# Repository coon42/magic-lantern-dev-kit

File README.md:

# magic-lantern-dev-kit
A dev kit for connection and communication with the service port of Canon EOS cameras.

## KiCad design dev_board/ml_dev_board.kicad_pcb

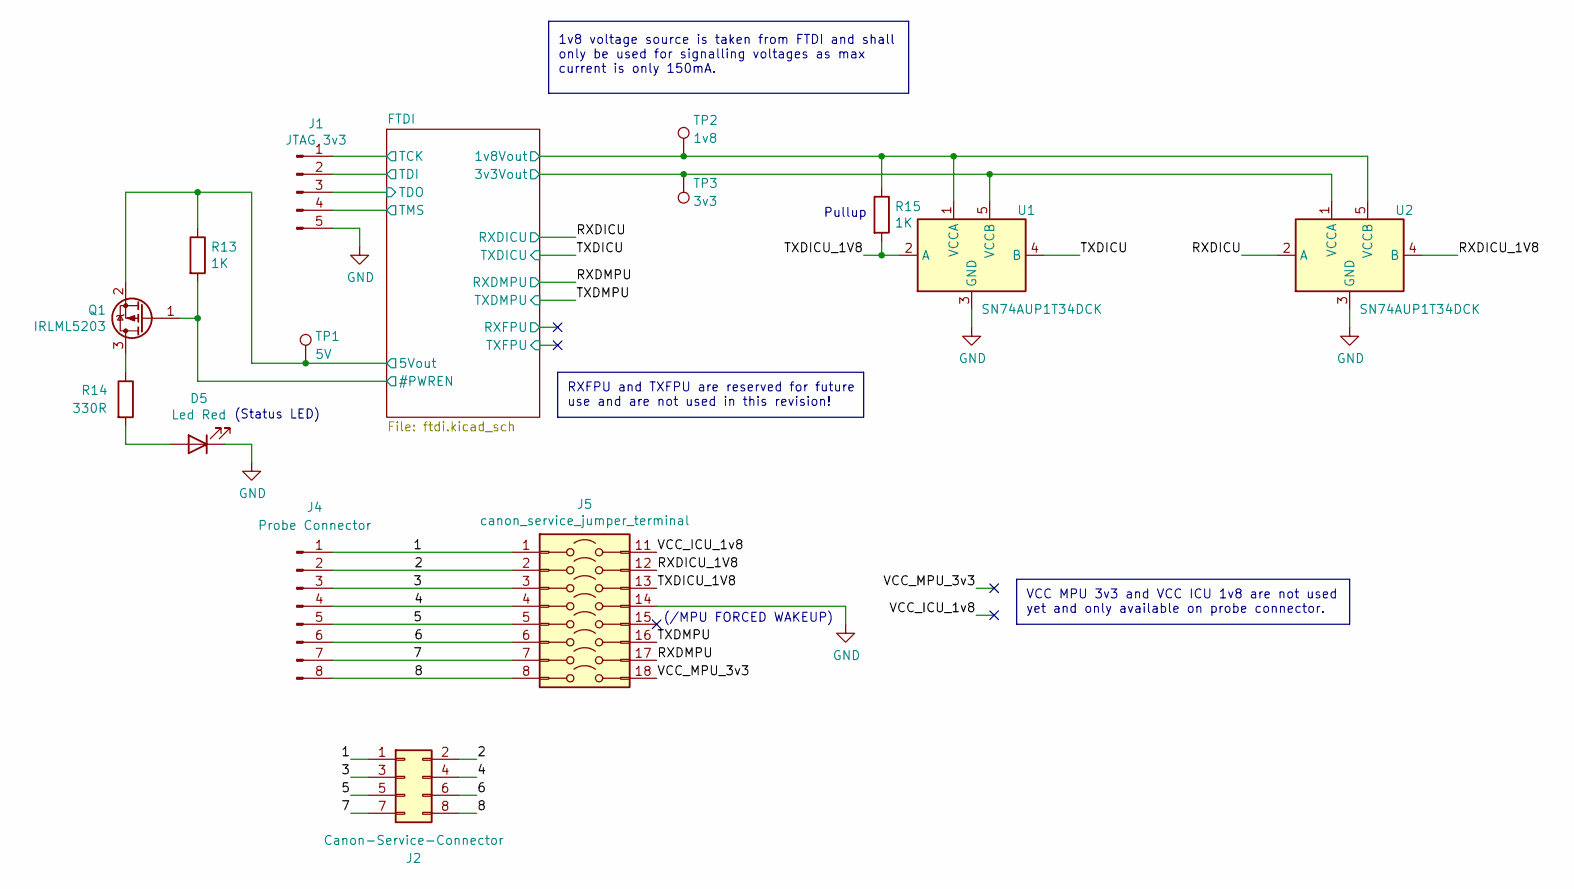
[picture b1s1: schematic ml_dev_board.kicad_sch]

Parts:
D5: Led Red; LED_0805_2012Metric
J1: JTAG 3v3; PinHeader_1x05_P2.54mm_Vertical_SMD_Pin1Left
J2: Canon-Service-Connector; IDC-Header_2x04_P2.54mm_Vertical
J4: Probe Connector; PinHeader_1x08_P2.54mm_Vertical_SMD_Pin1Left
J5: canon_service_jumper_terminal; PinHeader_2x08_P2.54mm_Vertical_Jumper_SMD
Q1: IRLML5203; SOT-23
R13, R15: 1K; R_0805_2012Metric
R14: 330R; R_0805_2012Metric
TP1: 5V; TestPoint_Pad_D1.5mm
TP2: 1v8; TestPoint_Pad_D1.5mm
TP3: 3v3; TestPoint_Pad_D1.5mm
U1, U2: SN74AUP1T34DCK; SOT-353_SC-70-5

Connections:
+1V8: R15.1, TP2.1, U1.1 (VCCA), U2.5 (VCCB); also elsewhere on the board
+3V3: TP3.1, U1.5 (VCCB), U2.1 (VCCA); also elsewhere on the board
+5V: Q1.2 (S), R13.1, TP1.1; also elsewhere on the board
/1: J2.1, J4.1, J5.1
/2: J2.2, J4.2, J5.2
/3: J2.3, J4.3, J5.3
/4: J2.4, J4.4, J5.4
/5: J2.5, J4.5, J5.5
/6: J2.6, J4.6, J5.6
/7: J2.7, J4.7, J5.7
/8: J2.8, J4.8, J5.8
/FTDI/#PWREN: Q1.1 (G), R13.2; also elsewhere on the board
/FTDI/TCK: J1.1; also elsewhere on the board
/FTDI/TDI: J1.2; also elsewhere on the board
/FTDI/TDO: J1.3; also elsewhere on the board
/FTDI/TMS: J1.4; also elsewhere on the board
/RXDICU: U2.2 (A); also elsewhere on the board
/RXDICU_1V8: J5.12, U2.4 (B)
/RXDMPU: J5.17; also elsewhere on the board
/TXDICU: U1.4 (B); also elsewhere on the board
/TXDICU_1V8: J5.13, R15.2, U1.2 (A)
/TXDMPU: J5.16; also elsewhere on the board
/VCC_ICU_1v8: J5.11
/VCC_MPU_3v3: J5.18
GND: D5.1 (K), J1.5, J5.14, U1.3 (GND), U2.3 (GND); also elsewhere on the board
unnamed: D5.2 (A), R14.2
unnamed: Q1.3 (D), R14.1

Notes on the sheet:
Pullup
RXFPU and TXFPU are reserved for future use and are not used in this revision!
(/MPU FORCED WAKEUP)
(Status LED)
1v8 voltage source is taken from FTDI and shall only be used for signalling voltages as max current is only 150mA.
VCC MPU 3v3 and VCC ICU 1v8 are not used yet and only available on probe connector.

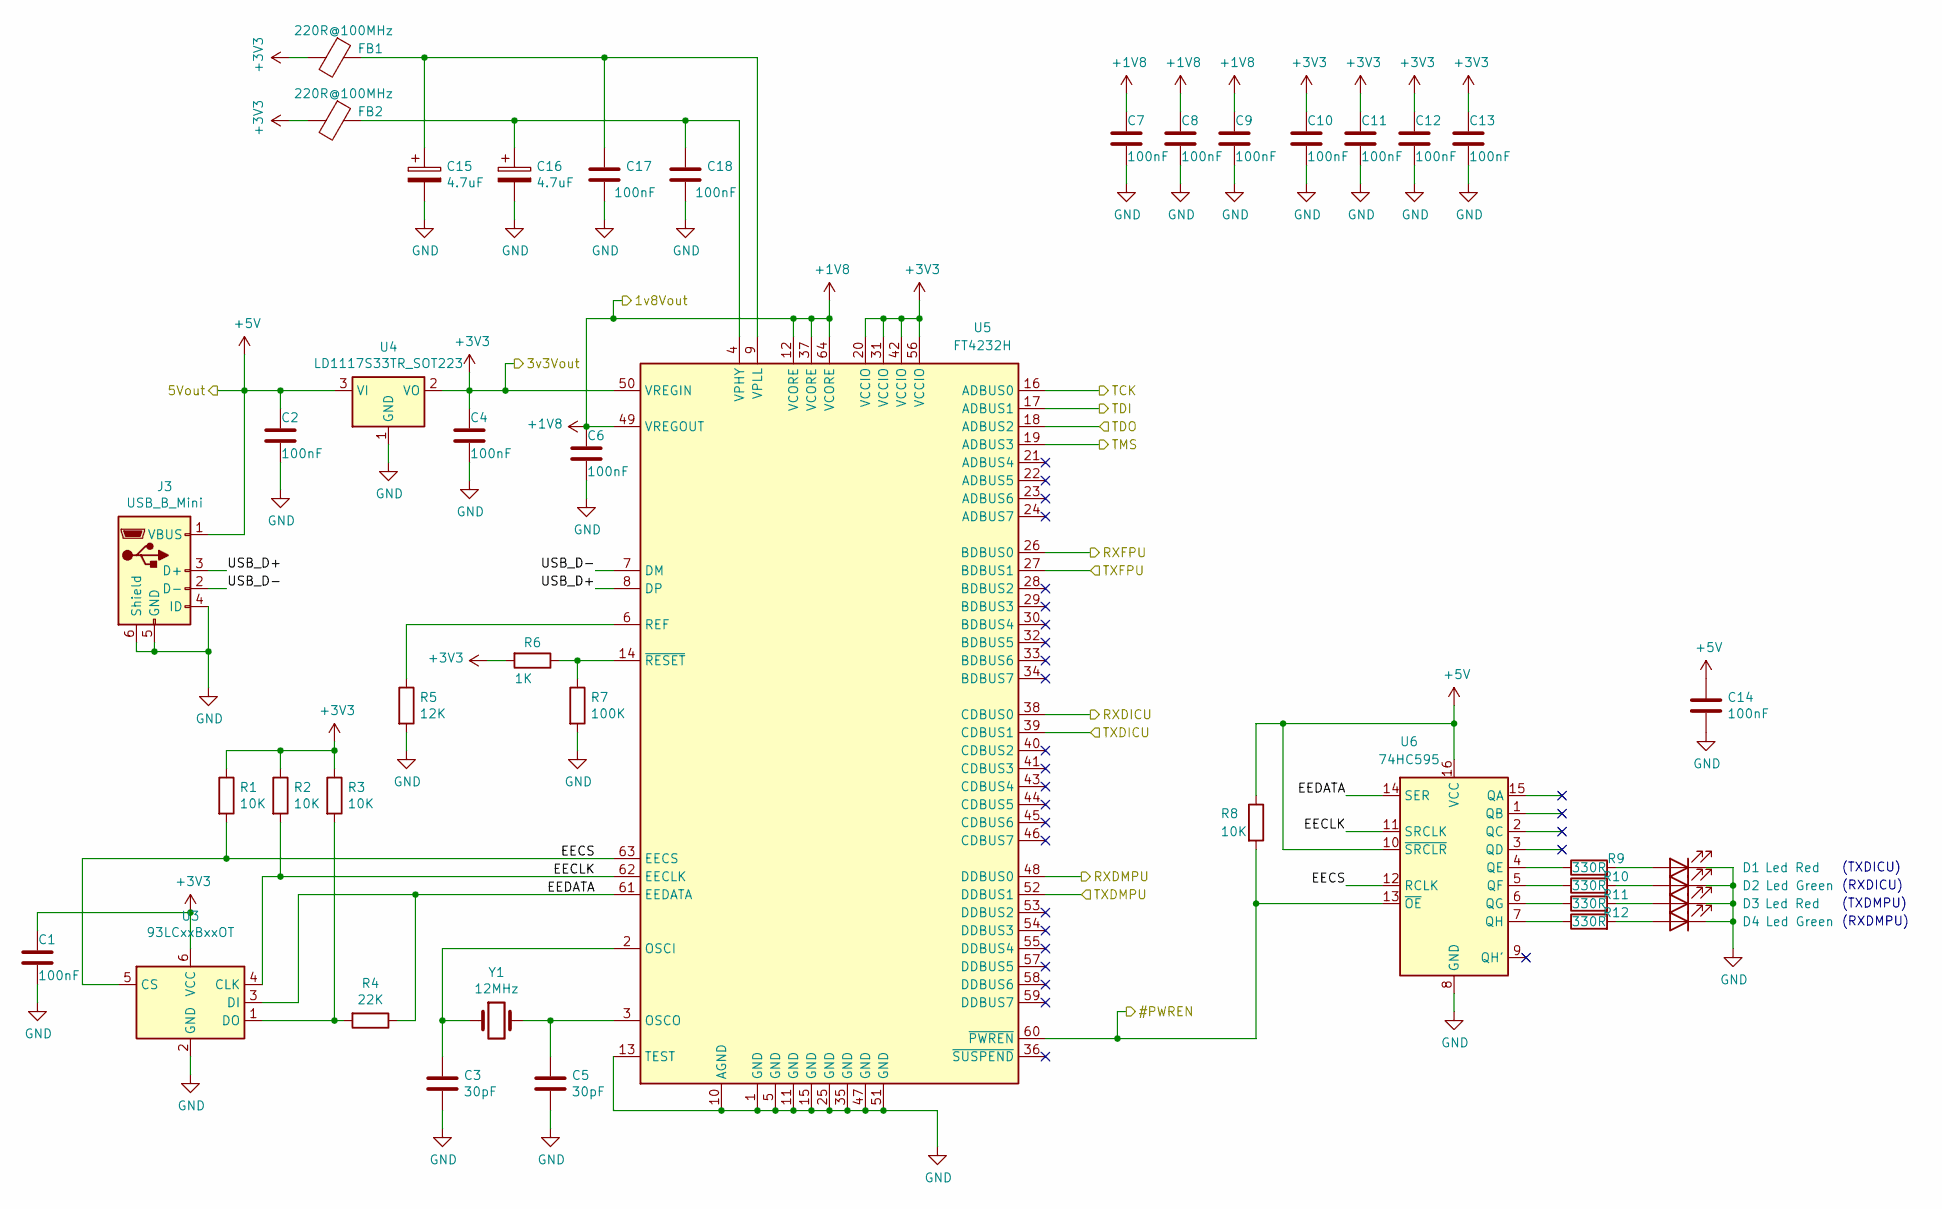
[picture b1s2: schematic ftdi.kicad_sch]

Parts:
C1, C2, C4, C6, C7, C8, C9, C10, C11, C12, C13, C14, C17, C18: 100nF; C_0805_2012Metric
C3, C5: 30pF; C_0805_2012Metric
C15, C16: 4.7uF; CP_EIA-3216-18_Kemet-A
D1, D3: Led Red; LED_0805_2012Metric
D2, D4: Led Green; LED_0805_2012Metric
FB1, FB2: 220R@100MHz; L_0805_2012Metric
J3: USB_B_Mini; USB_Mini-B_Lumberg_2486_01_Horizontal
R1, R2, R3, R8: 10K; R_0805_2012Metric
R4: 22K; R_0805_2012Metric
R5: 12K; R_0805_2012Metric
R6: 1K; R_0805_2012Metric
R7: 100K; R_0805_2012Metric
R9, R10, R11, R12: 330R; R_0805_2012Metric
U3: 93LCxxBxxOT; SOT-23-6
U4: LD1117S33TR_SOT223; SOT-223-3_TabPin2
U5: FT4232H; LQFP-64-1EP_10x10mm_P0.5mm_EP6.5x6.5mm_no_central_solder_pad
U6: 74HC595; TSSOP-16_4.4x5mm_P0.65mm
Y1: 12MHz; Crystal_SMD_TXC_7M-4Pin_3.2x2.5mm

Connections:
+1V8: C6.1, C7.1, C8.1, C9.1, U5.12 (VCORE), U5.37 (VCORE), U5.49 (VREGOUT), U5.64 (VCORE); also elsewhere on the board
+3V3: C1.1, C4.1, C10.1, C11.1, C12.1, C13.1, FB1.2, FB2.2, R1.1, R2.1, R3.1, R6.2, U3.6 (VCC), U4.2 (VO), U5.20 (VCCIO), U5.31 (VCCIO), U5.42 (VCCIO), U5.50 (VREGIN), U5.56 (VCCIO); also elsewhere on the board
+5V: C2.1, C14.1, J3.1 (VBUS), R8.1, U4.3 (VI), U6.10 (~SRCLR), U6.16 (VCC); also elsewhere on the board
/FTDI/#PWREN: R8.2, U5.60 (~PWREN), U6.13 (~OE); also elsewhere on the board
/FTDI/EECLK: R2.2, U3.4 (CLK), U5.62 (EECLK), U6.11 (SRCLK)
/FTDI/EECS: R1.2, U3.5 (CS), U5.63 (EECS), U6.12 (RCLK)
/FTDI/EEDATA: R4.1, U3.3 (DI), U5.61 (EEDATA), U6.14 (SER)
/FTDI/RXFPU: U5.26 (BDBUS0)
/FTDI/TCK: U5.16 (ADBUS0); also elsewhere on the board
/FTDI/TDI: U5.17 (ADBUS1); also elsewhere on the board
/FTDI/TDO: U5.18 (ADBUS2); also elsewhere on the board
/FTDI/TMS: U5.19 (ADBUS3); also elsewhere on the board
/FTDI/TXFPU: U5.27 (BDBUS1)
/FTDI/USB_D+: J3.3 (D+), U5.8 (DP)
/FTDI/USB_D-: J3.2 (D-), U5.7 (DM)
/RXDICU: U5.38 (CDBUS0); also elsewhere on the board
/RXDMPU: U5.48 (DDBUS0); also elsewhere on the board
/TXDICU: U5.39 (CDBUS1); also elsewhere on the board
/TXDMPU: U5.52 (DDBUS1); also elsewhere on the board
GND: C1.2, C2.2, C3.2, C4.2, C5.2, C6.2, C7.2, C8.2, C9.2, C10.2, C11.2, C12.2, C13.2, C14.2, C15.2, C16.2, C17.2, C18.2, D1.1 (K), D2.1 (K), D3.1 (K), D4.1 (K), J3.4 (ID), J3.5 (GND), J3.6 (Shield), R5.2, R7.2, U3.2 (GND), U4.1 (GND), U5.1 (GND), U5.5 (GND), U5.10 (AGND), U5.11 (GND), U5.13 (TEST), U5.15 (GND), U5.25 (GND), U5.35 (GND), U5.47 (GND), U5.51 (GND), U6.8 (GND); also elsewhere on the board
unnamed: D1.2 (A), R9.2
unnamed: D2.2 (A), R10.2
unnamed: D3.2 (A), R11.2
unnamed: D4.2 (A), R12.2
unnamed: R3.2, R4.2, U3.1 (DO)
unnamed: C3.1, U5.2 (OSCI), Y1.1
unnamed: C5.1, U5.3 (OSCO), Y1.2
unnamed: R5.1, U5.6 (REF)
unnamed: C16.1, C18.1, FB2.1, U5.4 (VPHY)
unnamed: C15.1, C17.1, FB1.1, U5.9 (VPLL)
unnamed: R6.1, R7.1, U5.14 (~RESET)
unnamed: R9.1, U6.4 (QE)
unnamed: R10.1, U6.5 (QF)
unnamed: R11.1, U6.6 (QG)
unnamed: R12.1, U6.7 (QH)

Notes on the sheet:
(RXDMPU)
(RXDICU)
(TXDICU)
(TXDMPU)

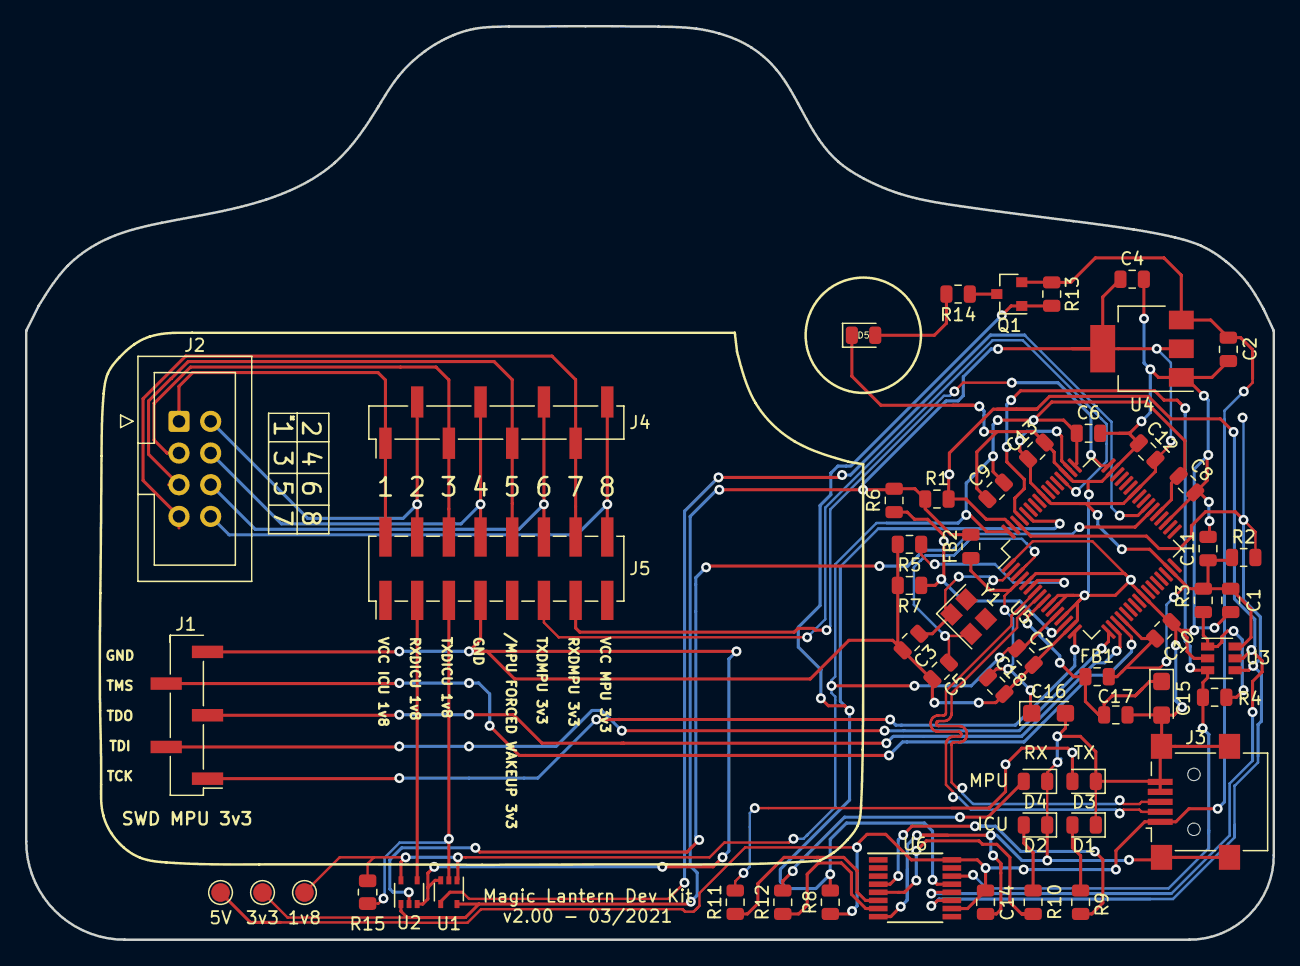
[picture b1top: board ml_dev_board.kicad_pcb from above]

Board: 2 copper layers, 100.0 x 73.2 mm, 56 parts (0 on the bottom side), 45 nets.

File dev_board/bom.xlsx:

Item | Quantity | Reference | Manufacturer | DigiKey Distrib. Part # | Description
 | 14 | C1, C2, C4, C6, C7, C8, C9, C10, C11, C12, C13, C14, C17, C18 |  | 399-1170-1-ND | 100nF
 | 2 | C3, C5 |  | 399-C0805C300M5HAC7800CT-ND | 30pF
 | 2 | C15, C16 |  | T491A475K006AT7280-ND | 4.7uF Tantalum
 | 3 | D1, D3, D5 |  | 350-2038-2-ND | Led Red
 | 2 | D2, D4 |  | 732-4986-1-ND | Led Green
 | 2 | FB1, FB2 |  | 445-1568-1-ND | 220R @ 100MHz
 | 1 | J1 |  | SAM12233-ND | 01x05 2.54mm pin header (JTAG)
 | 1 | J2 |  | 732-5395-ND | 02x04 2.54mm IDC header (service cable connector)
 | 1 | J3 |  | SAM8952-ND | USB B Mini
 | 1 | J4 |  | A122210-ND | 01x08 2.54mm pin header (Probe Connector)
 | 1 | J5 |  | 609-3486-2-ND | 02x08 2.54mm SMD pin header (Jumper terminal)
 | 1 | Q1 |  | IRLML5203TRPBFCT-ND | IRLML5203 P channel Mosfet (for status LED)
 | 4 | R1, R2, R3, R8 |  | 2019-RK73B2ATTD103JCT-ND | 10K
 | 1 | R4 |  | 2019-RK73B2ATTD223JCT-ND | 22K
 | 1 | R5 |  | 2019-RK73B2ATTD123JCT-ND | 12K
 | 3 | R6, R13, R15 |  | 2019-RK73H2ATTD1001FTR-ND | 1K
 | 1 | R7 |  | 2019-RK73B2ATTD104JCT-ND | 100K
 | 5 | R9, R10, R11, R12, R14 |  | 2019-RK73B2ATTD331JTR-ND | 330R
 | 2 | U1, U2 |  | 296-34900-1-ND | SN74AUP1T34DCK Logic Level Translator
 | 1 | U3 |  | 93LC56BT-I/OTCT-ND | 93LCxxBxxOT EEPROM
 | 1 | U4 |  | 497-1242-1-ND | LD1117S33TR_SOT223 3.3V linear regulator
 | 1 | U5 |  | 768-1026-1-ND | FT4232HL Quad FTDI
 | 1 | U6 |  | 296-23258-1-ND | 74HC595 shift register
 | 1 | Y1 |  | 887-1720-1-ND | 12Mhz crystal oscillator

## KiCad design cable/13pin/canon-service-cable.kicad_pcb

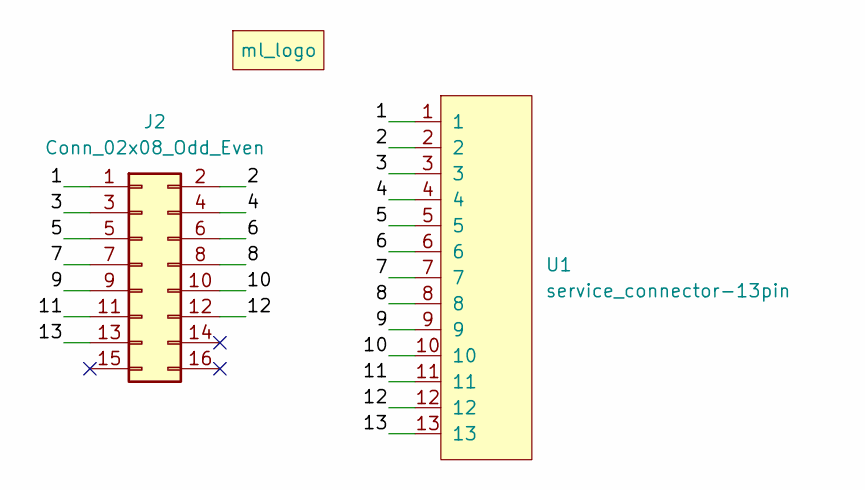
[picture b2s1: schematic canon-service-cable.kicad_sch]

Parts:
G1: ml_logo; logo
J2: Conn_02x08_Odd_Even; IDC-Header_2x08_P2.54mm_Horizontal
U1: service_connector-13pin; service_connector_pads_13pin

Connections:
/1: J2.1, U1.1
/2: J2.2, U1.2
/3: J2.3, U1.3
/4: J2.4, U1.4
/5: J2.5, U1.5
/6: J2.6, U1.6
/7: J2.7, U1.7
/8: J2.8, U1.8
/9: J2.9, U1.9
/10: J2.10, U1.10
/11: J2.11, U1.11
/12: J2.12, U1.12
/13: J2.13, U1.13

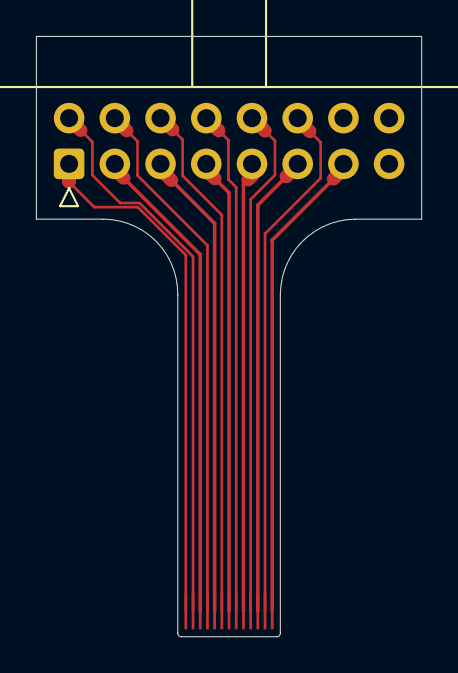
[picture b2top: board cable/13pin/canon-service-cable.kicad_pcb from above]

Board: 2 copper layers, 21.4 x 33.4 mm, 3 parts (1 on the bottom side), 13 nets.

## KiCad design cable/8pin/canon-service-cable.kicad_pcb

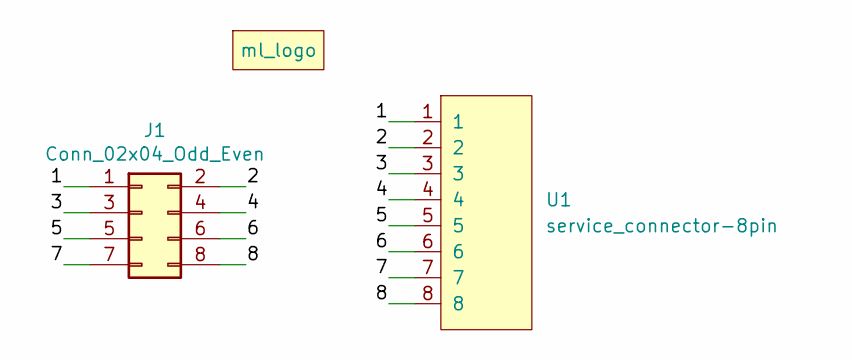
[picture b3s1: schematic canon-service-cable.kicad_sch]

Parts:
G1: ml_logo; logo
J1: Conn_02x04_Odd_Even; IDC-Header_2x04_P2.54mm_Horizontal
U1: service_connector-8pin; service_connector_pads_8pin

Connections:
/1: J1.1, U1.1
/2: J1.2, U1.2
/3: J1.3, U1.3
/4: J1.4, U1.4
/5: J1.5, U1.5
/6: J1.6, U1.6
/7: J1.7, U1.7
/8: J1.8, U1.8

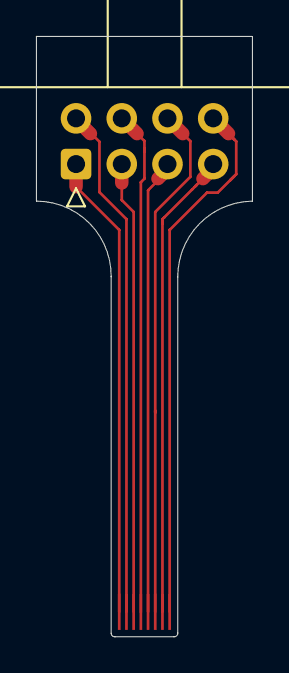
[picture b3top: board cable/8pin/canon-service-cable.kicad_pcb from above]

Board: 2 copper layers, 12.0 x 33.4 mm, 3 parts (1 on the bottom side), 8 nets.

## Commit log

2020-09-26 add kicad project of cable
2020-10-21 cable: adjust pad height from 3mm to 2.5mm
2020-10-21 cable: adjust connector width from 2.6mm to 2.7mm
2020-10-21 add dev_board project
2020-10-22 dev_board: add status led + test pads
2020-10-22 dev_board: add missing status LED resistor + fix silk
2020-10-24 dev_board: use tantalum footprints for polarized caps
2020-10-24 dev_board: fix service connector pinout / use straight connector + cosmetics
2020-11-30 dev_board: use correct footprint for tantalum caps
2020-11-30 cable: replace angled pin header by angled IDC header
2020-11-30 add .gitignore
2020-11-30 dev_board: add BOM
2020-11-30 Release: canon-service-cable v1.0
2020-11-30 cable: add v1.0 gerber files
2020-11-30 dev-board: add v1.0 gerber files
2020-11-30 .gitignore: add *.zip
2020-12-16 dev board: fix wrong parts on BOM
2020-12-16 dev board: fix mini usb symbol
2020-12-16 dev board: jumper terminal: move RXMPU from pin 5 to pin 7
2020-12-16 dev board: add 1v8 pullup resistor to TXICU pin
2020-12-16 dev board: fix silk screen for pin 5 and pin 7 (RXMPU)
2020-12-16 dev board: align ICU and MPU silk screen
2020-12-16 dev board: add RXMPU 1K pullup resistor to BOM
2020-12-16 dev board: rename JTAG 3.3V to JTAG 3v3
2020-12-16 dev board: route unconnected ground pin
2020-12-16 dev board: align TX and RX silk screen
2021-03-05 dev board: updated something on the bom
2021-03-05 dev board: added VCC ICU 1v8 + VCC MPU 3v3
2021-03-05 dev board: pcb: 3.3V -> 3v3, 1.8V -> 1v8
2021-03-05 dev board: pcb: update version number to v2.0
2021-12-10 dev board: ftdi: 3.3v -> 3v3
2021-12-10 dev board: add 1v8 max current warning
2022-03-05 add Kicad 5 project files
2022-03-05 cable: round up corners on connector
2022-03-05 cable: shorten contact pads a bit
2022-03-05 cable: update gerber files
2023-06-12 update kicad version
2025-09-06 move cable project files to 8pin subdir
2025-09-06 canon-service-cable: migrate kicad project to Kicad 9.0.4 + remove legacy project files
2025-09-06 canon-service-cable: rename footprint: canon-service-cable:service_connector_pads -> canon-service-cable:service_connector_pads_8pin
2025-09-06 canon-service-cable: migrate canon.lib -> canon.kicad_sym
2025-09-06 canon-service-cable: move footprints and symbols dir to parent dir
2025-09-06 canon-service-cable: 8pin: align pads to origin
2025-09-06 canon-service-cable: add footprint for 13pin cable
2025-09-06 canon-service-cable: add symbol for 13pin cable
2025-09-06 canon-service-cable: add project for 13 pin cable connector
2025-09-06 canon-service-cable: add gerber files for 13 pins variant
2025-09-07 cable: 13pin: add stiffner
2026-02-09 remove legacy ml_dev_board.pro file
2026-02-09 dev_board: update kicad project file + add MPU FORCED WAKEUP pin
2026-02-09 dev_board: pcb: rename JTAG 3v3 -> SWD MPU 3v3
